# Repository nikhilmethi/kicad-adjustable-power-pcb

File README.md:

# KiCad + SPICE: Adjustable Power Interface PCB

End-to-end circuit design, simulation, and PCB implementation of a voltage divider system, extended into a configurable analog output interface.

## Overview
This project implements a simple voltage regulation concept (9 V → ~5 V) and evolves it into a physically realizable PCB capable of producing an adjustable output voltage from 0–9 V.

The focus was on translating a basic circuit into a robust, manufacturable hardware design.

## Design Objectives
- Step down a 9 V input to a usable lower voltage  
- Maintain controlled current draw  
- Enable adjustable output for flexibility in downstream use  
- Transition from schematic design to a clean PCB layout  

## Circuit Design
- Designed a resistive voltage divider with clearly defined +9V, GND, and output (Vin) nets  
- Structured the schematic for clarity and correct power definition  
- Ensured electrical correctness through rule checking and validation  

## System Evolution
- Initial design: fixed voltage divider (~5 V output)  
- Final design: replaced fixed resistor with a **3-terminal potentiometer**, enabling a continuous output range from ~0 V to 9 V  

This shift prioritized flexibility and practical usability over a single operating point.

## PCB Implementation
- Single-sided, through-hole PCB (50 mm × 50 mm)  
- Ground plane for improved stability and routing simplicity  
- External interfaces:
  - 9 V input via connector
  - Vin/GND output for integration with other systems  
- Mechanical considerations:
  - Standard mounting holes for integration into larger systems  

## Key Takeaways
- Bridging circuit theory to hardware requires layout, grounding, and interfacing considerations beyond schematic design  
- Simple circuits can be made significantly more useful through small design changes (e.g., fixed → adjustable output)  
- PCB constraints (size, routing, connectors) directly influence design decisions  

## Files
- KiCad schematic and PCB layout  
- SPICE simulation files (used for validation)

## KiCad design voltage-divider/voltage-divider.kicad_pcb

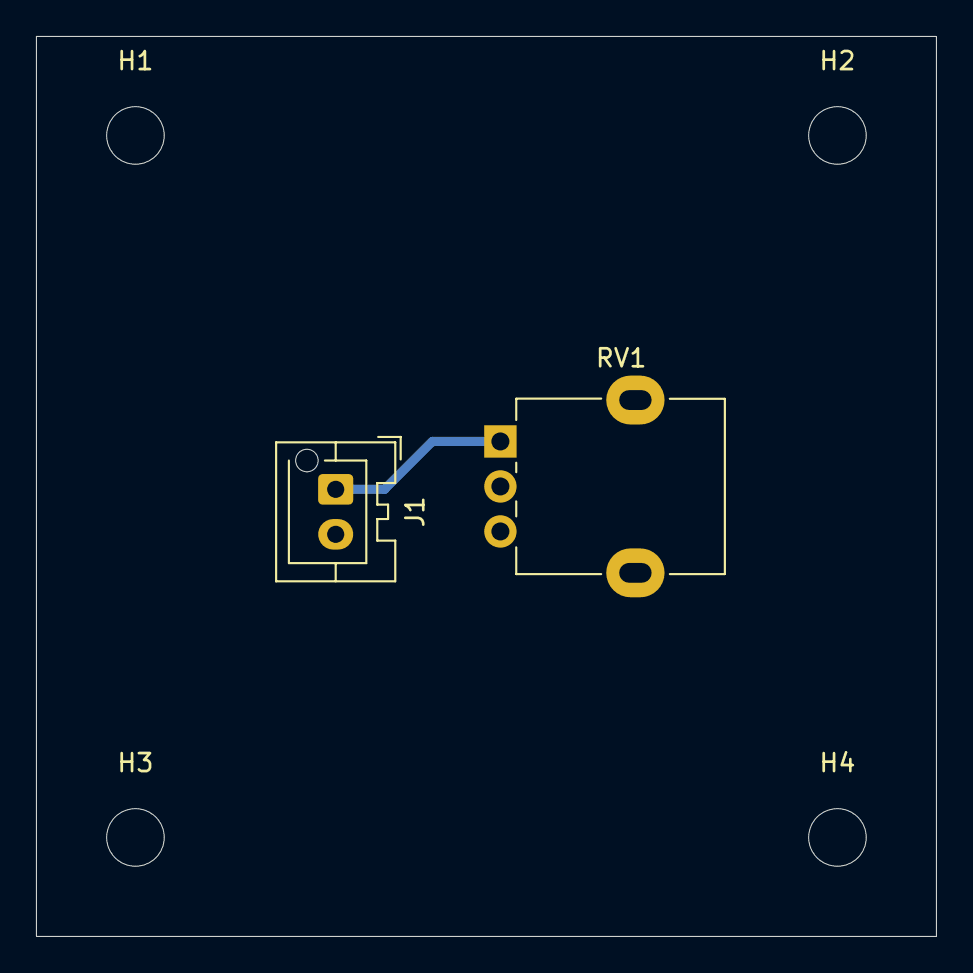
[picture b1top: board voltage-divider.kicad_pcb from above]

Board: 2 copper layers, 50.0 x 50.0 mm, 6 parts (0 on the bottom side), 2 nets.

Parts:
H1, H2, H3, H4: MountingHole; MountingHole_3.2mm_M3
J1: Conn_01x02_Pin; JST_XA_B02B-XASK-1-A_1x02_P2.50mm_Vertical
RV1: R_Potentiometer_US; Potentiometer_Alpha_RD901F-40-00D_Single_Vertical

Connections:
+9V: J1.1, RV1.1
GND: J1.2, RV1.3

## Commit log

2026-02-04 initial commit of KiCAD / SPICE lab
2026-02-04 add section for the PCB layout
2026-02-04 add latest checkpoint of KiCad project files
2026-02-04 add DRC and CI tests
2026-02-05 Schematic is passing ERC
2026-02-05 Successful SPICE Simulation
2026-02-05 Updated SPICE workbook with DC sweep
2026-02-05 Added metadata to schematic
2026-02-17 Updated schematic to include potentiometer and created PCB layout
2026-04-27 Revise README for project clarity and updates
    Updated project overview, design objectives, and key takeaways. Removed outdated instructions and added new sections for circuit design and PCB implementation.
